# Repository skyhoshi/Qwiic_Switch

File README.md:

SparkFun Qwiic Switch/Arcade
========================================
<table class="table table-hover table-striped table-bordered">
  <tr align="center">
   <td></td>
   <td></td>
   <td></td>
  </tr>
  <tr align="center">
    <td><a href="https://www.sparkfun.com/products/15591">SparkFun Qwiic Arcade - Red (SPX-15591)</a></td>
    <td><a href="https://www.sparkfun.com/products/15592">SparkFun Qwiic Arcade - Blue (SPX-15592)</a></td>
    <td><a href="https://www.sparkfun.com/products/15586">SparkFun Qwiic Switch (SPX-15586)</a></td>
  </tr>
</table>

The SparkFun Qwiic Switch and Qwiic Arcade are I<sup>2</sup>C enabled boards with interrupts, variable I<sup>2</sup>C addresses, external LED output, and onboard button queues.

Repository Contents
-------------------

* **/Firmware** - Firmware for the built-in ATTiny84 on the Qwiic Button/Switch/Arcade (.h, .ino)
* **/Hardware** - Eagle design files (.brd, .sch)
* **/Hardware/Production** - Production panel files (.brd)

Documentation
--------------
* **[SparkFun Qwiic Button Arduino Library](https://github.com/sparkfun/SparkFun_Qwiic_Button_Arduino_Library)** - Arduino library for the Qwiic Button and Switch.

License Information
-------------------

This product is _**open source**_! 

Please review the LICENSE.md file for license information. 

If you have any questions or concerns on licensing, please contact technical support on our [SparkFun forums](https://forum.sparkfun.com/viewforum.php?f=152).

Distributed as-is; no warranty is given.

- Your friends at SparkFun.

_<COLLABORATION CREDIT>_

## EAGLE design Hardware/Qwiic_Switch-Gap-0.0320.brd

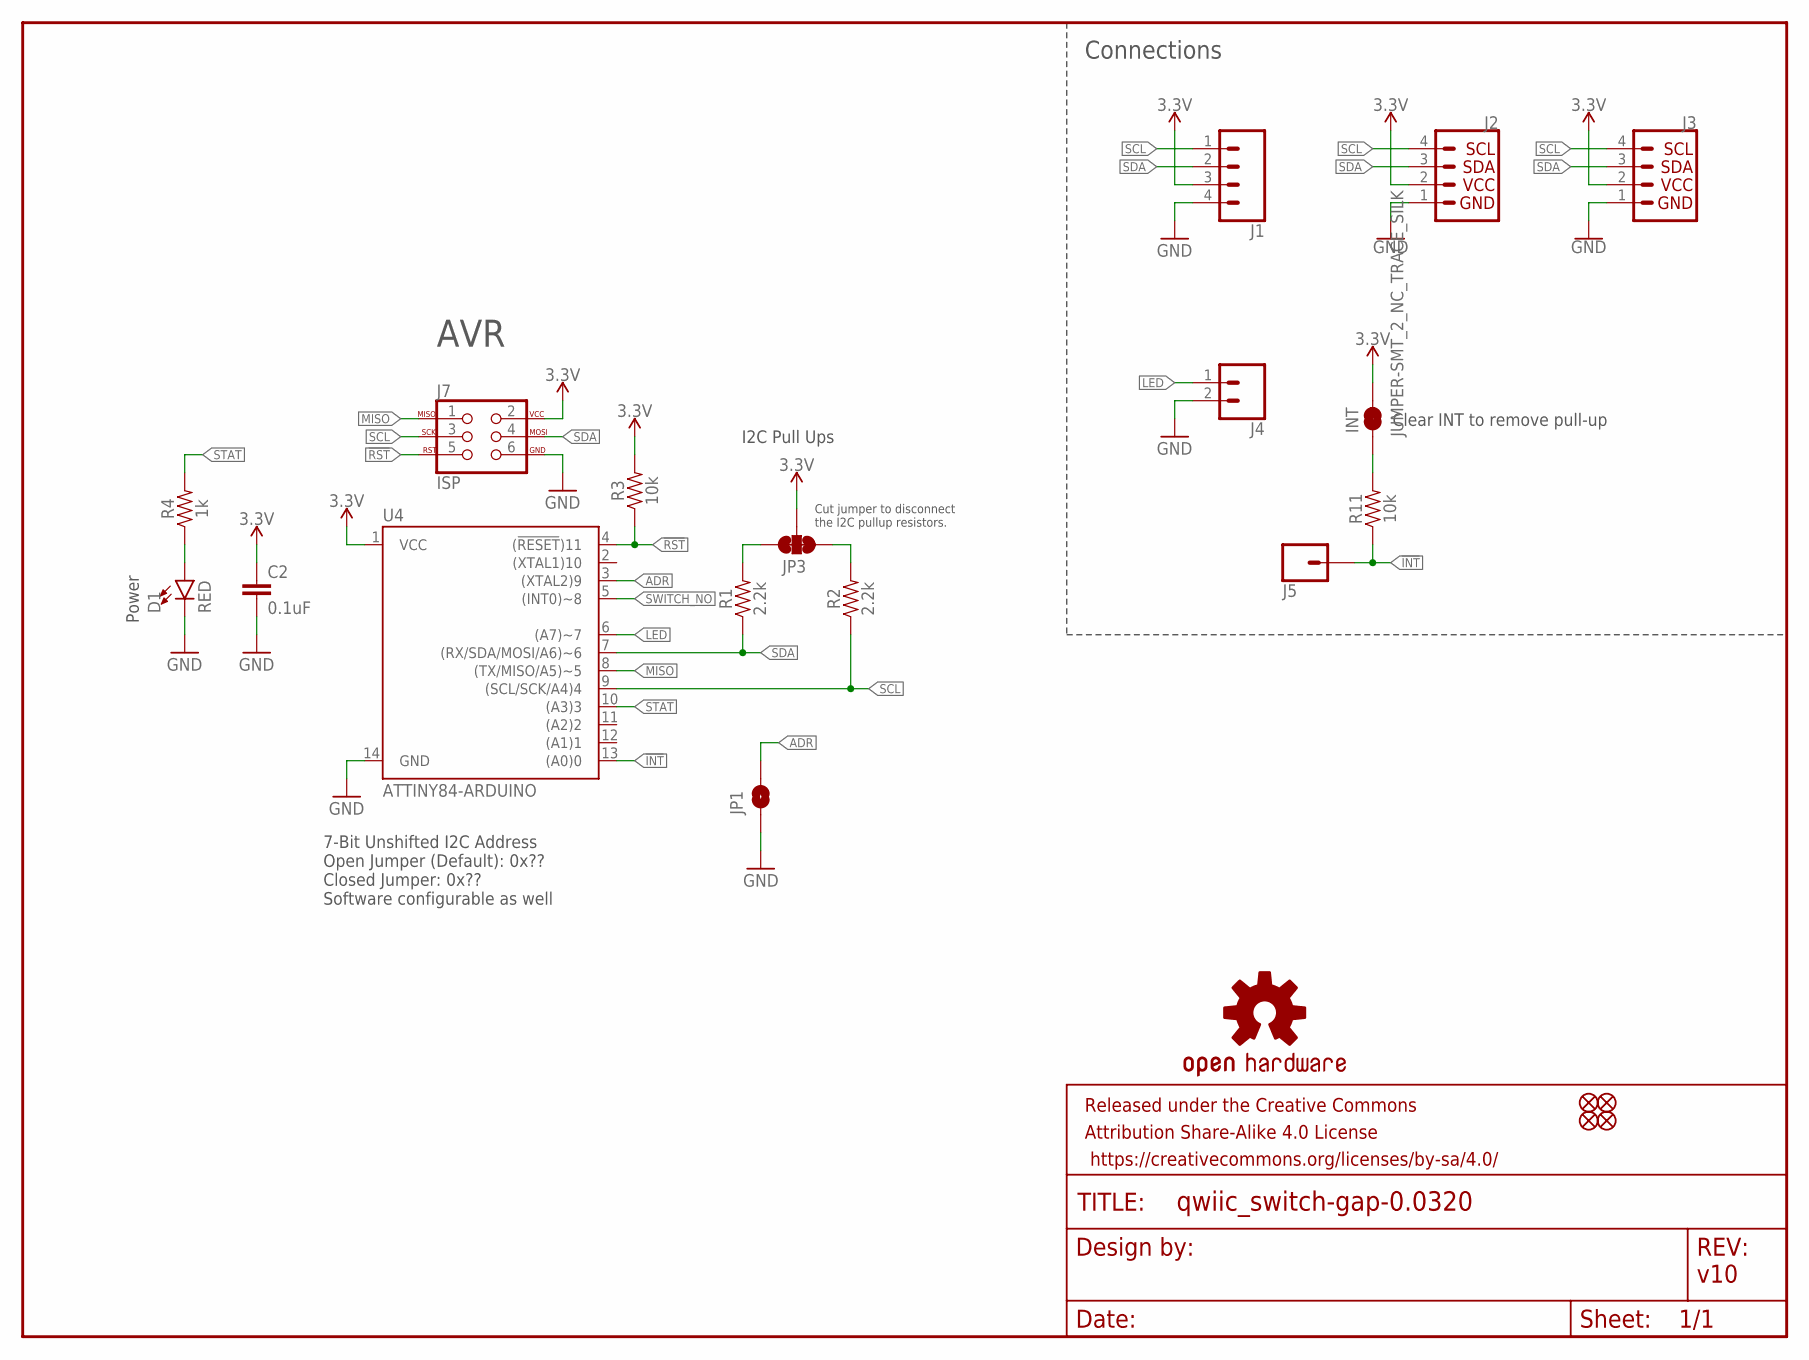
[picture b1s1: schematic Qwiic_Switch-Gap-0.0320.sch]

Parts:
C2: 0.1uF; 0603
D1: RED; LED-0603
FRAME1: FRAME-LETTER; CREATIVE_COMMONS
INT: JUMPER-SMT_2_NC_TRACE_SILK; SMT-JUMPER_2_NC_TRACE_SILK
J1: CONN_041X04_NO_SILK; 1X04_NO_SILK
J2, J3: QWIIC_CONNECTORJS-1MM; JST04_1MM_RA
J4: CONN_021X02_NO_SILK; 1X02_NO_SILK
J5: CONN_01PTH_NO_SILK_YES_STOP; 1X01_NO_SILK
J7: ISP; 2X3_TEST_POINTS
JP1: JUMPER-SMT_2_NO_SILK; SMT-JUMPER_2_NO_SILK
JP2, JP6, JP8, JP9: FIDUCIALUFIDUCIAL; MICRO-FIDUCIAL
JP3: JUMPER-SMT_3_2-NC_TRACE_SILK; SMT-JUMPER_3_2-NC_TRACE_SILK
LOGO1: OSHW-LOGOMINI; OSHW-LOGO-MINI
R1, R2: 2.2k; 0603
R3, R11: 10k; 0603
R4: 1k; 0603
U4: ATTINY84-ARDUINO; SO14

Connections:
3.3V: C2.1, INT.2, J1.3, J2.2, J3.2, J7.2, JP3.2, R3.2, U4.1 (VCC)
!INT: J5.1, R11.1, U4.13 ((A0)0)
!RST: J7.5, R3.1, U4.4 ((!RESET!)11)
ADR: JP1.2, U4.3 ((XTAL2)9)
GND: C2.2, D1.C, J1.4, J2.1, J3.1, J4.2, J7.6, JP1.1, U4.14 (GND)
INT_R: INT.1, R11.2
LED: J4.1, U4.6 ((A7)~7)
MISO: J7.1, U4.8 ((TX/MISO/A5)~5)
unnamed: D1.A, R4.1
SCL: J1.1, J2.4, J3.4, J7.3, R2.1, U4.9 ((SCL/SCK/A4)4)
SCL_PU1: JP3.1, R2.2
SDA: J1.2, J2.3, J3.3, J7.4, R1.1, U4.7 ((RX/SDA/MOSI/A6)~6)
SDA_PU1: JP3.3, R1.2
STAT: R4.2, U4.10 ((A3)3)
SWITCH_NO: U4.5 ((INT0)~8)

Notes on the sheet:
v10
Connections
Cut jumper to disconnect the I2C pullup resistors.
7-Bit Unshifted I2C Address Open Jumper (Default): 0x?? Closed Jumper: 0x?? Software configurable as well
I2C Pull Ups
AVR
Power
Clear INT to remove pull-up

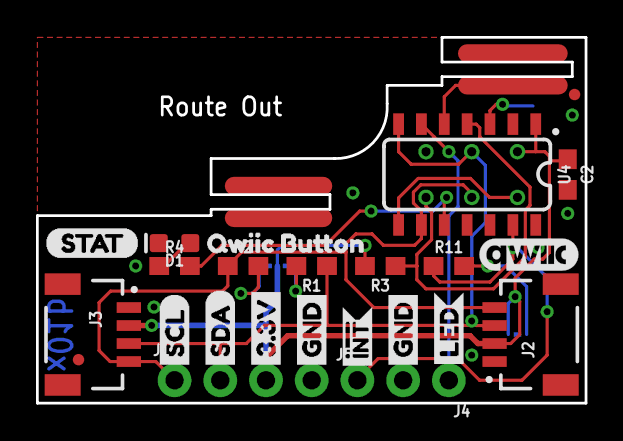
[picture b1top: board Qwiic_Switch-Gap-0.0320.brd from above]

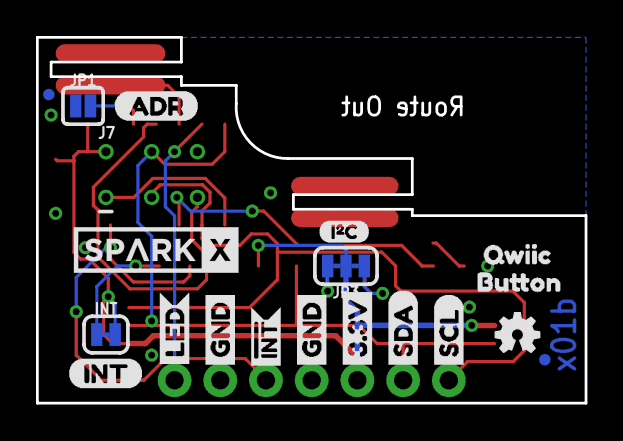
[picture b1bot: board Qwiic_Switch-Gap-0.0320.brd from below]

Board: 2 copper layers, 30.5 x 20.3 mm, 47 parts (20 on the bottom side), 14 nets.

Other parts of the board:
U$1, U$23: BUTTON1
U$2, U$20: QWIIC0
U$3, U$19: LED2
U$4: INT-()-04
U$5, U$14: SCL
U$6, U$12: SDA
U$7, U$22: 3.3V
U$8, U$13, U$16, U$17: GND
U$9: (ADR)
U$10: I_SUPER2_C-()-03
U$11, U$15: INT#-[<-04
U$18: SPARKX-MEDIUM
U$21: STAT1
U$24: QWIIC_5.5MM

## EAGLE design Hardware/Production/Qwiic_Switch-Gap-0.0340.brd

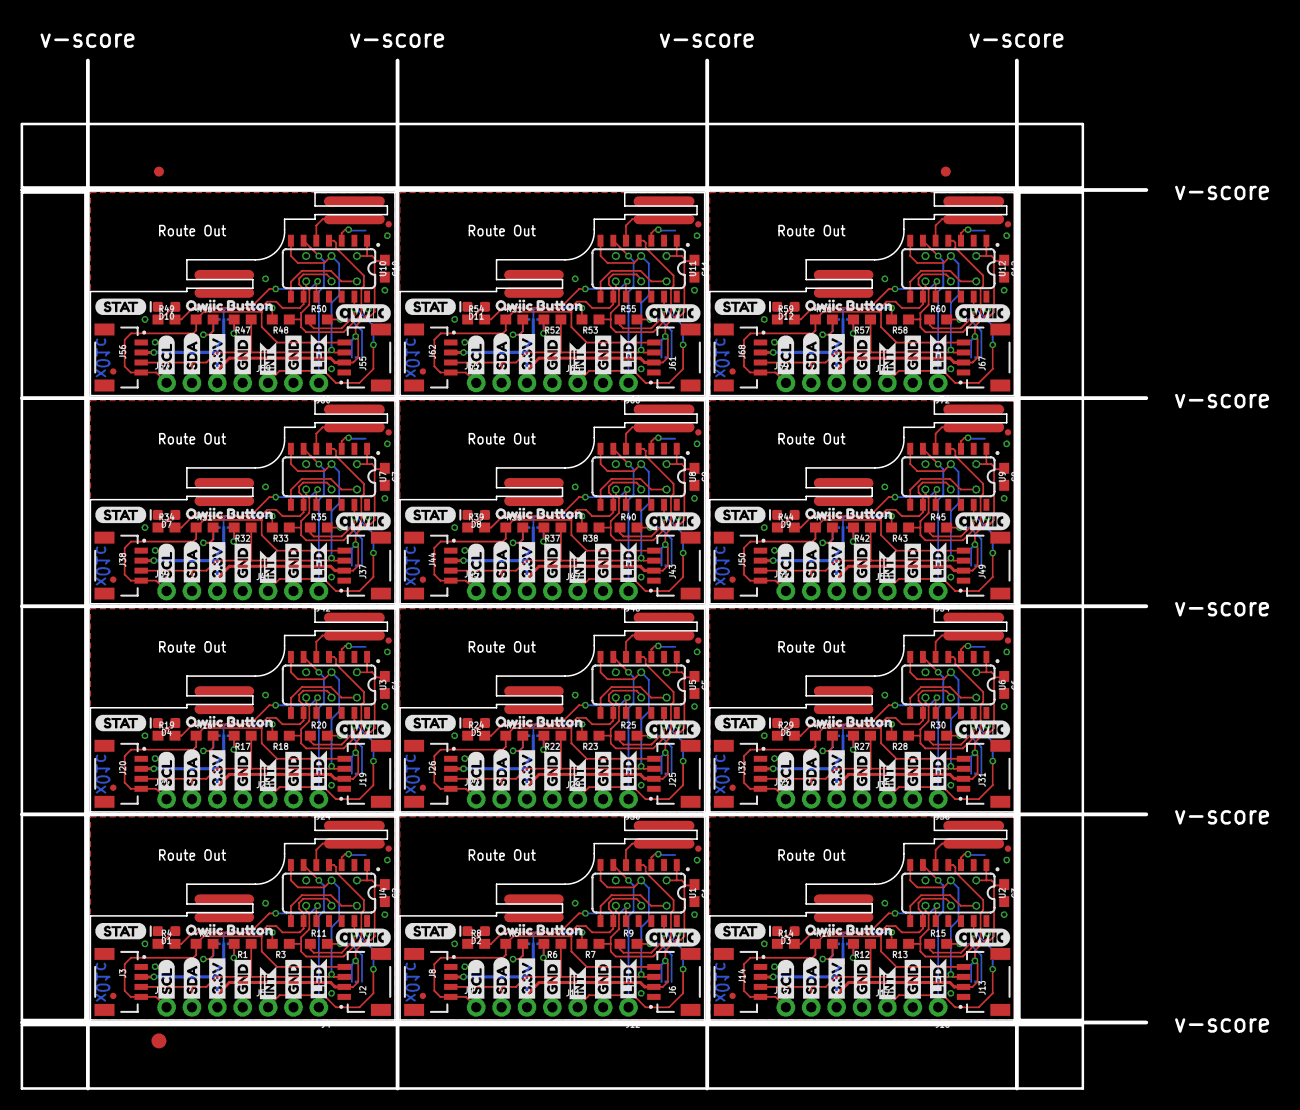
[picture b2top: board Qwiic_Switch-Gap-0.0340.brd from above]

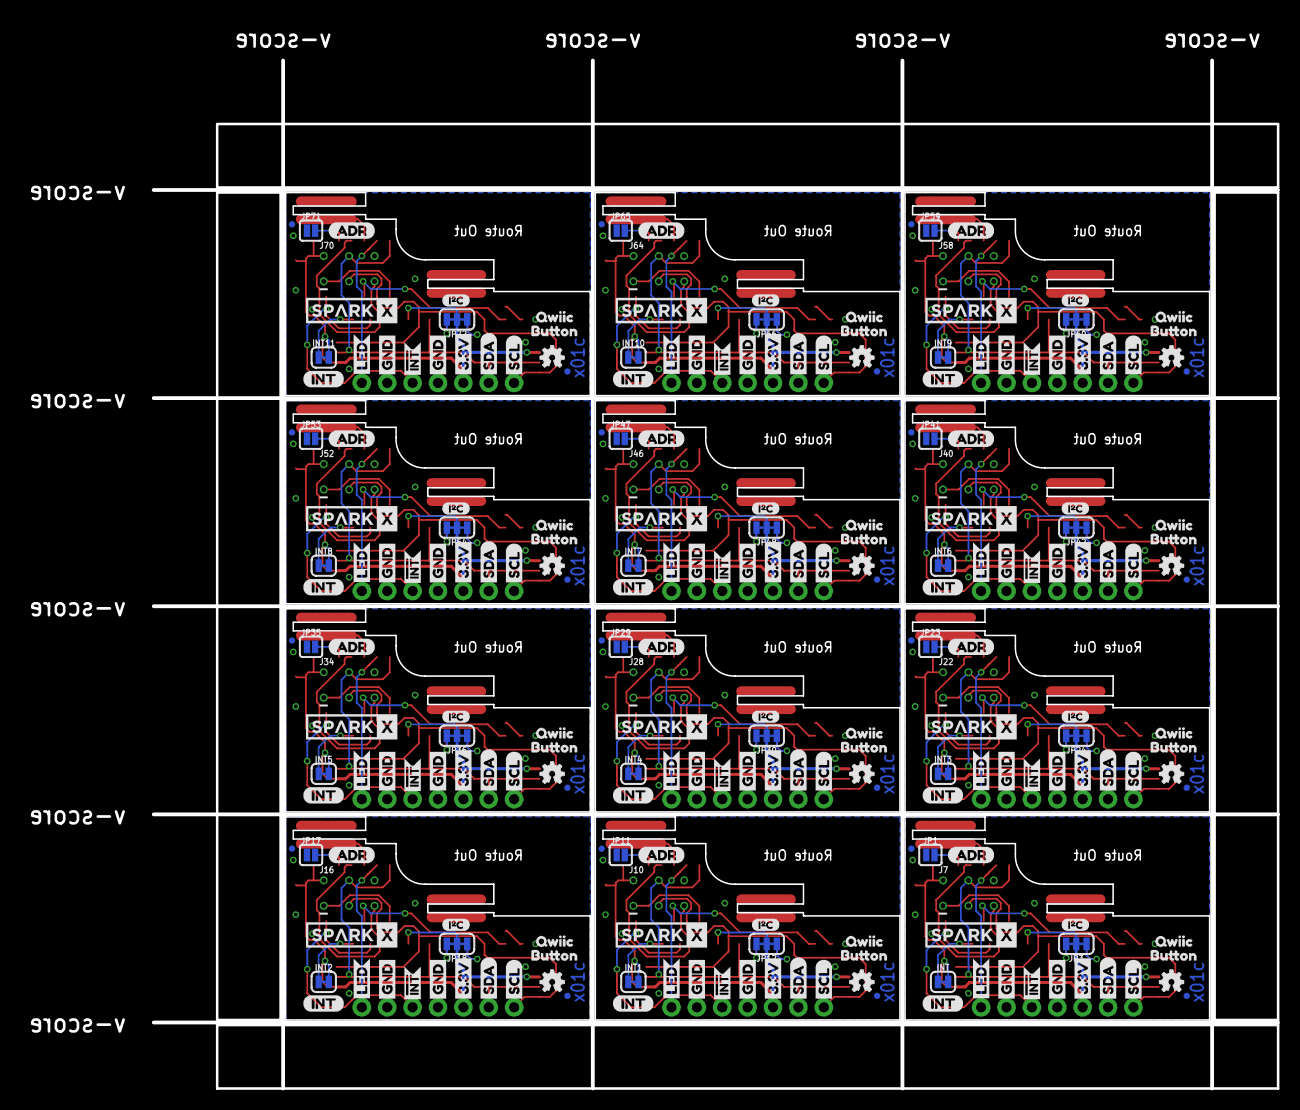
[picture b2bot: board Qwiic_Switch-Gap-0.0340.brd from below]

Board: 2 copper layers, 112.5 x 102.9 mm, 555 parts (240 on the bottom side), 168 nets.

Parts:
C1, C2, C3, C4, C5, C6, C7, C8, C9, C10, C11, C12: 0.1uF; 0603
D1, D2, D3, D4, D5, D6, D7, D8, D9, D10, D11, D12: RED; LED-0603
E$1, E$2: FIDUCIAL-1X2
E$3: FIDUCIAL-1.5X3
INT, INT1, INT2, INT3, INT4, INT5, INT6, INT7, INT8, INT9, INT10, INT11: JUMPER-SMT_2_NC_TRACE_SILK; SMT-JUMPER_2_NC_TRACE_SILK
J1, J9, J15, J21, J27, J33, J39, J45, J51, J57, J63, J69: 1X04_NO_SILK
J2, J3, J6, J8, J13, J14, J19, J20, J25, J26, J31, J32, J37, J38, J43, J44, J49, J50, J55, J56, J61, J62, J67, J68: JST04_1MM_RA
J4, J12, J18, J24, J30, J36, J42, J48, J54, J60, J66, J72: 1X02_NO_SILK
J5, J11, J17, J23, J29, J35, J41, J47, J53, J59, J65, J71: 1X01_NO_SILK
J7, J10, J16, J22, J28, J34, J40, J46, J52, J58, J64, J70: ISP; 2X3_TEST_POINTS
JP1, JP11, JP17, JP23, JP29, JP35, JP41, JP47, JP53, JP59, JP65, JP71: SMT-JUMPER_2_NO_SILK
JP2, JP4, JP5, JP6, JP7, JP8, JP9, JP10, JP13, JP14, JP15, JP16, JP19, JP20, JP21, JP22, JP25, JP26, JP27, JP28, JP31, JP32, JP33, JP34, JP37, JP38, JP39, JP40, JP43, JP44, JP45, JP46, JP49, JP50, JP51, JP52, JP55, JP56, JP57, JP58, JP61, JP62, JP63, JP64, JP67, JP68, JP69, JP70: FIDUCIALUFIDUCIAL; MICRO-FIDUCIAL
JP3, JP12, JP18, JP24, JP30, JP36, JP42, JP48, JP54, JP60, JP66, JP72: SMT-JUMPER_3_2-NC_TRACE_SILK
LOGO1, LOGO2, LOGO3, LOGO4, LOGO5, LOGO6, LOGO7, LOGO8, LOGO9, LOGO10, LOGO11, LOGO12: OSHW-LOGOMINI; OSHW-LOGO-MINI
R1, R2, R5, R6, R10, R12, R16, R17, R21, R22, R26, R27, R31, R32, R36, R37, R41, R42, R46, R47, R51, R52, R56, R57: 2.2k; 0603
R3, R7, R9, R11, R13, R15, R18, R20, R23, R25, R28, R30, R33, R35, R38, R40, R43, R45, R48, R50, R53, R55, R58, R60: 10k; 0603
R4, R8, R14, R19, R24, R29, R34, R39, R44, R49, R54, R59: 1k; 0603
U1, U2, U3, U4, U5, U6, U7, U8, U9, U10, U11, U12: ATTINY84-ARDUINO; SO14
U$1, U$23, U$44, U$47, U$68, U$71, U$92, U$95, U$116, U$119, U$140, U$143, U$164, U$167, U$188, U$191, U$212, U$215, U$236, U$239, U$260, U$263, U$284, U$287: QWIIC0
U$2, U$20, U$45, U$46, U$69, U$70, U$93, U$94, U$117, U$118, U$141, U$142, U$165, U$166, U$189, U$190, U$213, U$214, U$237, U$238, U$261, U$262, U$285, U$286: BUTTON1
U$3, U$19, U$41, U$42, U$65, U$66, U$89, U$90, U$113, U$114, U$137, U$138, U$161, U$162, U$185, U$186, U$209, U$210, U$233, U$234, U$257, U$258, U$281, U$282: LED2
U$4, U$40, U$64, U$88, U$112, U$136, U$160, U$184, U$208, U$232, U$256, U$280: INT-()-04
U$5, U$14, U$25, U$35, U$49, U$59, U$73, U$83, U$97, U$107, U$121, U$131, U$145, U$155, U$169, U$179, U$193, U$203, U$217, U$227, U$241, U$251, U$265, U$275: SCL
U$6, U$12, U$26, U$34, U$50, U$58, U$74, U$82, U$98, U$106, U$122, U$130, U$146, U$154, U$170, U$178, U$194, U$202, U$218, U$226, U$242, U$250, U$266, U$274: SDA
U$7, U$22, U$27, U$31, U$51, U$55, U$75, U$79, U$99, U$103, U$123, U$127, U$147, U$151, U$171, U$175, U$195, U$199, U$219, U$223, U$243, U$247, U$267, U$271: 3.3V
U$8, U$13, U$16, U$17, U$28, U$30, U$37, U$38, U$52, U$54, U$61, U$62, U$76, U$78, U$85, U$86, U$100, U$102, U$109, U$110, U$124, U$126, U$133, U$134, U$148, U$150, U$157, U$158, U$172, U$174, U$181, U$182, U$196, U$198, U$205, U$206, U$220, U$222, U$229, U$230, U$244, U$246, U$253, U$254, U$268, U$270, U$277, U$278: GND
U$9, U$29, U$53, U$77, U$101, U$125, U$149, U$173, U$197, U$221, U$245, U$269: (ADR)
U$10, U$32, U$56, U$80, U$104, U$128, U$152, U$176, U$200, U$224, U$248, U$272: I_SUPER2_C-()-03
U$11, U$15, U$33, U$36, U$57, U$60, U$81, U$84, U$105, U$108, U$129, U$132, U$153, U$156, U$177, U$180, U$201, U$204, U$225, U$228, U$249, U$252, U$273, U$276: INT#-[<-04
U$18, U$39, U$63, U$87, U$111, U$135, U$159, U$183, U$207, U$231, U$255, U$279: SPARKX-MEDIUM
U$21, U$43, U$67, U$91, U$115, U$139, U$163, U$187, U$211, U$235, U$259, U$283: STAT1
U$24, U$48, U$72, U$96, U$120, U$144, U$168, U$192, U$216, U$240, U$264, U$288: QWIIC_5.5MM

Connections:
3.3V: C2.1, INT.2, J1.3, J2.2, J3.2, J7.2, JP3.2, R3.2, U4.1
3.3V1: C1.1, INT1.2, J6.2, J8.2, J9.3, J10.2, JP12.2, R7.2, U1.1
3.3V2: C3.1, INT2.2, J13.2, J14.2, J15.3, J16.2, JP18.2, R13.2, U2.1
3.3V3: C4.1, INT3.2, J19.2, J20.2, J21.3, J22.2, JP24.2, R18.2, U3.1
3.3V4: C5.1, INT4.2, J25.2, J26.2, J27.3, J28.2, JP30.2, R23.2, U5.1
3.3V5: C6.1, INT5.2, J31.2, J32.2, J33.3, J34.2, JP36.2, R28.2, U6.1
3.3V6: C7.1, INT6.2, J37.2, J38.2, J39.3, J40.2, JP42.2, R33.2, U7.1
3.3V7: C8.1, INT7.2, J43.2, J44.2, J45.3, J46.2, JP48.2, R38.2, U8.1
3.3V8: C9.1, INT8.2, J49.2, J50.2, J51.3, J52.2, JP54.2, R43.2, U9.1
3.3V9: C10.1, INT9.2, J55.2, J56.2, J57.3, J58.2, JP60.2, R48.2, U10.1
3.3V10: C11.1, INT10.2, J61.2, J62.2, J63.3, J64.2, JP66.2, R53.2, U11.1
3.3V11: C12.1, INT11.2, J67.2, J68.2, J69.3, J70.2, JP72.2, R58.2, U12.1
!INT: J5.1, R11.1, U4.13
!INT1: J11.1, R9.1, U1.13
!INT2: J17.1, R15.1, U2.13
!INT3: J23.1, R20.1, U3.13
!INT4: J29.1, R25.1, U5.13
!INT5: J35.1, R30.1, U6.13
!INT6: J41.1, R35.1, U7.13
!INT7: J47.1, R40.1, U8.13
!INT8: J53.1, R45.1, U9.13
!INT9: J59.1, R50.1, U10.13
!INT10: J65.1, R55.1, U11.13
!INT11: J71.1, R60.1, U12.13
!RST: J7.5, R3.1, U4.4
!RST1: J10.5, R7.1, U1.4
!RST2: J16.5, R13.1, U2.4
!RST3: J22.5, R18.1, U3.4
!RST4: J28.5, R23.1, U5.4
!RST5: J34.5, R28.1, U6.4
!RST6: J40.5, R33.1, U7.4
!RST7: J46.5, R38.1, U8.4
!RST8: J52.5, R43.1, U9.4
!RST9: J58.5, R48.1, U10.4
!RST10: J64.5, R53.1, U11.4
!RST11: J70.5, R58.1, U12.4
ADR: JP1.2, U4.3
ADR1: JP11.2, U1.3
ADR2: JP17.2, U2.3
ADR3: JP23.2, U3.3
ADR4: JP29.2, U5.3
ADR5: JP35.2, U6.3
ADR6: JP41.2, U7.3
ADR7: JP47.2, U8.3
ADR8: JP53.2, U9.3
ADR9: JP59.2, U10.3
ADR10: JP65.2, U11.3
ADR11: JP71.2, U12.3
GND: C2.2, D1.C, J1.4, J2.1, J3.1, J4.2, J7.6, JP1.1, U4.14
GND1: C1.2, D2.C, J6.1, J8.1, J9.4, J10.6, J12.2, JP11.1, U1.14
GND2: C3.2, D3.C, J13.1, J14.1, J15.4, J16.6, J18.2, JP17.1, U2.14
GND3: C4.2, D4.C, J19.1, J20.1, J21.4, J22.6, J24.2, JP23.1, U3.14
GND4: C5.2, D5.C, J25.1, J26.1, J27.4, J28.6, J30.2, JP29.1, U5.14
GND5: C6.2, D6.C, J31.1, J32.1, J33.4, J34.6, J36.2, JP35.1, U6.14
GND6: C7.2, D7.C, J37.1, J38.1, J39.4, J40.6, J42.2, JP41.1, U7.14
GND7: C8.2, D8.C, J43.1, J44.1, J45.4, J46.6, J48.2, JP47.1, U8.14
GND8: C9.2, D9.C, J49.1, J50.1, J51.4, J52.6, J54.2, JP53.1, U9.14
GND9: C10.2, D10.C, J55.1, J56.1, J57.4, J58.6, J60.2, JP59.1, U10.14
GND10: C11.2, D11.C, J61.1, J62.1, J63.4, J64.6, J66.2, JP65.1, U11.14
GND11: C12.2, D12.C, J67.1, J68.1, J69.4, J70.6, J72.2, JP71.1, U12.14
INT_R: INT.1, R11.2
INT_R1: INT1.1, R9.2
INT_R2: INT2.1, R15.2
INT_R3: INT3.1, R20.2
INT_R4: INT4.1, R25.2
INT_R5: INT5.1, R30.2
INT_R6: INT6.1, R35.2
INT_R7: INT7.1, R40.2
INT_R8: INT8.1, R45.2
INT_R9: INT9.1, R50.2
INT_R10: INT10.1, R55.2
INT_R11: INT11.1, R60.2
LED: J4.1, U4.6
LED1: J12.1, U1.6
LED2: J18.1, U2.6
LED3: J24.1, U3.6
LED4: J30.1, U5.6
LED5: J36.1, U6.6
LED6: J42.1, U7.6
LED7: J48.1, U8.6
LED8: J54.1, U9.6
LED9: J60.1, U10.6
LED10: J66.1, U11.6
LED11: J72.1, U12.6
MISO: J7.1, U4.8
MISO1: J10.1, U1.8
MISO2: J16.1, U2.8
MISO3: J22.1, U3.8
MISO4: J28.1, U5.8
MISO5: J34.1, U6.8
MISO6: J40.1, U7.8
MISO7: J46.1, U8.8
MISO8: J52.1, U9.8
MISO9: J58.1, U10.8
MISO10: J64.1, U11.8
MISO11: J70.1, U12.8
unnamed: D2.A, R8.1
unnamed: D1.A, R4.1
unnamed: D3.A, R14.1
unnamed: D4.A, R19.1
unnamed: D5.A, R24.1
unnamed: D6.A, R29.1
unnamed: D7.A, R34.1
unnamed: D8.A, R39.1
unnamed: D9.A, R44.1
unnamed: D10.A, R49.1
unnamed: D11.A, R54.1
unnamed: D12.A, R59.1
SCL: J1.1, J2.4, J3.4, J7.3, R2.1, U4.9
SCL1: J6.4, J8.4, J9.1, J10.3, R5.1, U1.9
SCL2: J13.4, J14.4, J15.1, J16.3, R10.1, U2.9
SCL3: J19.4, J20.4, J21.1, J22.3, R16.1, U3.9
SCL4: J25.4, J26.4, J27.1, J28.3, R21.1, U5.9
SCL5: J31.4, J32.4, J33.1, J34.3, R26.1, U6.9
SCL6: J37.4, J38.4, J39.1, J40.3, R31.1, U7.9
SCL7: J43.4, J44.4, J45.1, J46.3, R36.1, U8.9
SCL8: J49.4, J50.4, J51.1, J52.3, R41.1, U9.9
SCL9: J55.4, J56.4, J57.1, J58.3, R46.1, U10.9
SCL10: J61.4, J62.4, J63.1, J64.3, R51.1, U11.9
SCL11: J67.4, J68.4, J69.1, J70.3, R56.1, U12.9
SCL_PU1: JP3.1, R2.2
SCL_PU2: JP12.1, R5.2
SCL_PU3: JP18.1, R10.2
SCL_PU4: JP24.1, R16.2
SCL_PU5: JP30.1, R21.2
SCL_PU6: JP36.1, R26.2
SCL_PU7: JP42.1, R31.2
SCL_PU8: JP48.1, R36.2
SCL_PU9: JP54.1, R41.2
SCL_PU10: JP60.1, R46.2
SCL_PU11: JP66.1, R51.2
SCL_PU12: JP72.1, R56.2
SDA: J1.2, J2.3, J3.3, J7.4, R1.1, U4.7
SDA1: J6.3, J8.3, J9.2, J10.4, R6.1, U1.7
SDA2: J13.3, J14.3, J15.2, J16.4, R12.1, U2.7
SDA3: J19.3, J20.3, J21.2, J22.4, R17.1, U3.7
SDA4: J25.3, J26.3, J27.2, J28.4, R22.1, U5.7
SDA5: J31.3, J32.3, J33.2, J34.4, R27.1, U6.7
SDA6: J37.3, J38.3, J39.2, J40.4, R32.1, U7.7
SDA7: J43.3, J44.3, J45.2, J46.4, R37.1, U8.7
SDA8: J49.3, J50.3, J51.2, J52.4, R42.1, U9.7
SDA9: J55.3, J56.3, J57.2, J58.4, R47.1, U10.7
SDA10: J61.3, J62.3, J63.2, J64.4, R52.1, U11.7
SDA11: J67.3, J68.3, J69.2, J70.4, R57.1, U12.7
SDA_PU1: JP3.3, R1.2
SDA_PU2: JP12.3, R6.2
SDA_PU3: JP18.3, R12.2
SDA_PU4: JP24.3, R17.2
SDA_PU5: JP30.3, R22.2
SDA_PU6: JP36.3, R27.2
SDA_PU7: JP42.3, R32.2
SDA_PU8: JP48.3, R37.2
SDA_PU9: JP54.3, R42.2
SDA_PU10: JP60.3, R47.2
SDA_PU11: JP66.3, R52.2
SDA_PU12: JP72.3, R57.2
STAT: R4.2, U4.10
STAT1: R8.2, U1.10
STAT2: R14.2, U2.10
STAT3: R19.2, U3.10
STAT4: R24.2, U5.10
STAT5: R29.2, U6.10
STAT6: R34.2, U7.10
STAT7: R39.2, U8.10
STAT8: R44.2, U9.10
STAT9: R49.2, U10.10
STAT10: R54.2, U11.10
STAT11: R59.2, U12.10

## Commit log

2019-06-11 Rename files with gap sizes.
2019-06-11 Removing files with too large gap
    Gap of 0.03 is still too loose on switch paddles. Removing gaps 0.032 and 0.034.
2019-07-23 Reworked stack, updated bitwise operators with readable macros
2019-07-24 Moved queue functions to a separate header file
    No functionality changed, just cleaned up the code.
2019-07-24 Moved the register memory map to a separate header file
    No functionality changed, just code restructure
2019-07-24 Struct-ified the LED handling and moved it to it's own header file
    Also went from byte to uint8_t for cross-platform compatibility
2019-07-24 Update interrupts.ino
    Go from bytes to uint8_t for cross-platform compatibility
2019-07-26 Moved some functionality into header files, refactored register mapping
    Also slowly progressing towards compliance with the Google C++ style manual so that's good :+1:
2019-07-26 Removed janky debug serial.print()'s
2019-07-27 Fixed spelling
2019-07-29 Removed config for interrupt logic level
    Turns out the board is designed to do active-low only
2019-07-30 Fixed issue where queues would not default to being empty
2019-07-31 Added ability to switch I2C addresses, and updated documentation
    I2C address selection should be correct based on being on either the Switch or the Button
2019-08-01 Revert "Added ability to switch I2C addresses, and updated documentation"
    This reverts commit 4302c0fba5622e3d9719b3ecffc95f3a24247165.
2019-08-01 Made EEPROM reads and writes pointer-based
2019-08-01 Device ID and I2C addresses are now selectedable from a #define
2019-08-01 Updated documentation, everything works on testing platform
2019-08-01 Removed stack-based debounce from interrupts
    It was interfering with the interrupt on button press :/ but everything works on the qwiic button!
2019-08-01 Fixed button debouncing
2019-08-01 Set firmware version equal to 1.0
    This is the production code that is going on the devices
2019-08-08 Added automated flashing capability
2019-08-08 Add verification script
2019-08-09 Fix firmware button debouncing issues
2019-08-14 Correct I2C address logic to match schematic. Reorder memoryMap to match register map doc.
2019-08-20 Add debouce to pin change interrupt.
2019-08-20 Declaring Ques as volatile. Removing multiple I2C addresses. Removing multiple hardware defs.
2019-08-20 Use EEPROM put instead of update. Was probably causing EEPROM corruption.
    Update() only handles 8-bit values. Put handles 8, 16, and 32 correctly while calling update() on the 8-bit chunks.
2019-08-20 Rename firmware to Qwiic_Button
2019-08-28 Remove duplicate files
2019-08-28 Add ADR jumpers. Decrease leaf switch gap to 0.025". Remove old files.
2019-08-29 Update schematic with I2C address
2019-09-03 Update ignore. Remove backup files
2019-09-06 Corrected bit order of interruptConfig
    This code erases EEPROM settings on Arduino Unos. Found out that the compiler packs bits in an unexpected order.
2019-09-06 Finished fixing bit order
    For all unions.
2019-09-10 Change I2C addres working!
    Moved startI2C call to evaluate no matter the i2c address value in recordSystemSettings function.
2019-09-11 Fixed start i2C bug
    Originally we were calling startI2C everytime recordSystemSettings was called (loop()). Now, we only call startI2C after checking if the I2C address has actually been changed.
2019-09-12 Changed interruptConfigure.status to buttonStatus.eventAvailable
    Whether an event has ocurred is a detail of the current button status, so I changed the registers accordingly. Additionally, changed the interrupt pin logic in the main loop.
2019-09-12 Set interrupt pin to default high
2019-09-17 External interrupts
    Moved the interruptPin logic outside of the updateFlag check. pressedEnable and clickedEnable default to true.
2019-09-18 Update LED AFTER recordSystemSettings
    Fixed weird flashing of LED that occurs in example 3.
2019-09-20 Added EEPROM_erase sketch for uploading code to fresh buttons
    Generated appropriate .hex files and updated .bat file.
2020-01-16 Increase programming speed to 1MHz

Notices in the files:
parts and their libraries:
SparkFun-Capacitors: Licensing: Creative Commons ShareAlike 4.0 International - https://creativecommons.org/licenses/by-sa/4.0
SparkFun-Aesthetics: Released under the Creative Commons Attribution Share-Alike 4.0 License
SparkFun-Aesthetics: https://creativecommons.org/licenses/by-sa/4.0
